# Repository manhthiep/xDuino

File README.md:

xDuino
======

Collection of Arduino-compatible boards

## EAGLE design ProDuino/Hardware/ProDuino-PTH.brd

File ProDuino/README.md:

ProDuino
======

ProDuino - Arduino-compatible board without USB port.

Original design: [SparkFun's Arduino Pro 328](https://www.sparkfun.com/products/10915)

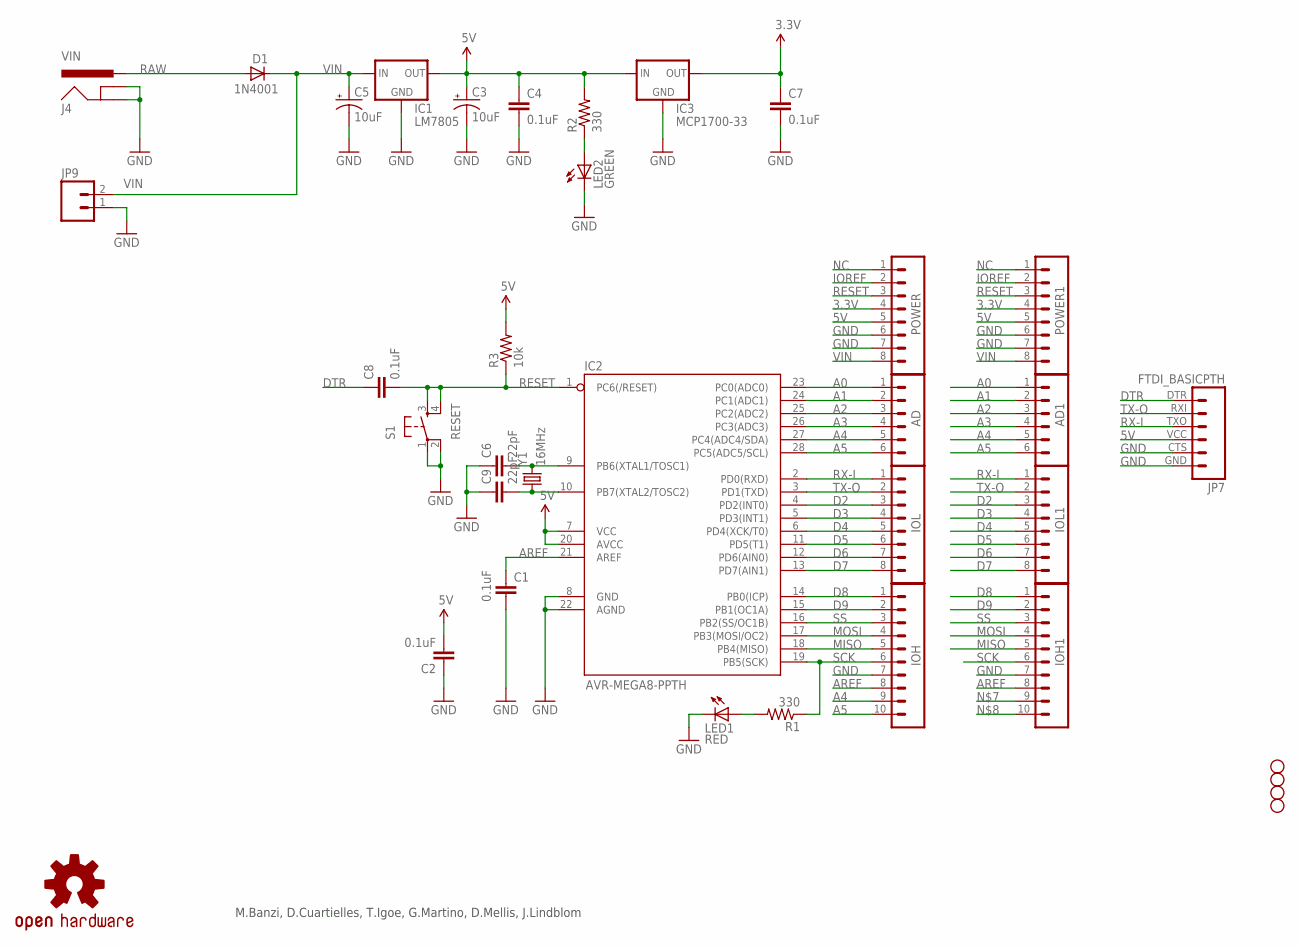
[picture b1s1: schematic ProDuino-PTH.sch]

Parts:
AD, AD1: M06SIP; 1X06
C1, C2, C4, C7, C8: 0.1uF; CAP-PTH-SMALL2
C3, C5: 10uF; CPOL-RADIAL-10UF-25V
C6, C9: 22pF; CAP-PTH-SMALL2
D1: 1N4001; DIODE-1N4001
IC1: LM7805; TO-220-ALT
IC2: AVR-MEGA8-PPTH; DIL28-3
IC3: MCP1700-33; TO-92
IOH, IOH1: M10"; 1X10
IOL, IOL1: M081X08; 1X08
J4: VIN; POWER_JACK_PTH_LOCK
JP3, JP4, JP5, JP6: STAND-OFF
JP7: FTDI_BASICPTH; FTDI_BASIC
JP9: M02POLAR; MOLEX-1X2
LED1: RED; LED5MM
LED2: GREEN; LED5MM
POWER, POWER1: M081X08; 1X08
R1, R2: 330; AXIAL-0.3
R3: 10k; AXIAL-0.3
S1: RESET; TACTILE-PTH
U$7: OSHW-LOGOM; OSHW-LOGO-M
Y1: 16MHz; HC49US

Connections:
3.3V: C7.1, IC3.3 (OUT), POWER.4, POWER1.4
5V: C2.2, C3.1 (+), C4.1, IC1.OUT, IC2.7 (VCC), IC2.20 (AVCC), IC3.2 (IN), JP7.VCC (4), POWER.5, POWER1.5, R2.P$2 (2), R3.P$2 (2)
A0: AD.1, AD1.1, IC2.23 (PC0(ADC0))
A1: AD.2, AD1.2, IC2.24 (PC1(ADC1))
A2: AD.3, AD1.3, IC2.25 (PC2(ADC2))
A3: AD.4, AD1.4, IC2.26 (PC3(ADC3))
A4: AD.5, AD1.5, IC2.27 (PC4(ADC4/SDA)), IOH.9
A5: AD.6, AD1.6, IC2.28 (PC5(ADC5/SCL)), IOH.10
AREF: C1.1, IC2.21 (AREF), IOH.8, IOH1.8
D2: IC2.4 (PD2(INT0)), IOL.3, IOL1.3
D3: IC2.5 (PD3(INT1)), IOL.4, IOL1.4
D4: IC2.6 (PD4(XCK/T0)), IOL.5, IOL1.5
D5: IC2.11 (PD5(T1)), IOL.6, IOL1.6
D6: IC2.12 (PD6(AIN0)), IOL.7, IOL1.7
D7: IC2.13 (PD7(AIN1)), IOL.8, IOL1.8
D8: IC2.14 (PB0(ICP)), IOH.1, IOH1.1
D9: IC2.15 (PB1(OC1A)), IOH.2, IOH1.2
DTR: C8.1, JP7.DTR (1)
GND: C1.2, C2.1, C3.2 (-), C4.2, C5.2 (-), C6.1, C7.2, C9.1, IC1.GND, IC2.8 (GND), IC2.22 (AGND), IC3.1 (GND), IOH.7, IOH1.7, J4.GND, J4.GNDBREAK, JP7.CTS (5), JP7.GND (6), JP9.1, LED1.K (C), LED2.K (C), POWER.6, POWER.7, POWER1.6, POWER1.7, S1.1, S1.2
IOREF: POWER.2, POWER1.2
MISO: IC2.18 (PB4(MISO)), IOH.5, IOH1.5
MOSI: IC2.17 (PB3(MOSI/OC2)), IOH.4, IOH1.4
unnamed: LED1.A, R1.P$2 (2)
unnamed: LED2.A, R2.P$1 (1)
unnamed: C6.2, IC2.9 (PB6(XTAL1/TOSC1)), Y1.2
unnamed: C9.2, IC2.10 (PB7(XTAL2/TOSC2)), Y1.1
NC: POWER.1, POWER1.1
RAW: D1.A, J4.PWR
RESET: C8.2, IC2.1 (PC6(/RESET)), POWER.3, POWER1.3, R3.P$1 (1), S1.3, S1.4
RX-I: IC2.2 (PD0(RXD)), IOL.1, IOL1.1, JP7.TXO (3)
SCK: IC2.19 (PB5(SCK)), IOH.6, IOH1.6, R1.P$1 (1)
SS: IC2.16 (PB2(SS/OC1B)), IOH.3, IOH1.3
TX-O: IC2.3 (PD1(TXD)), IOL.2, IOL1.2, JP7.RXI (2)
VIN: C5.1 (+), D1.C, IC1.IN, JP9.2, POWER.8, POWER1.8

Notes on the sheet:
M.Banzi, D.Cuartielles, T.Igoe, G.Martino, D.Mellis, J.Lindblom

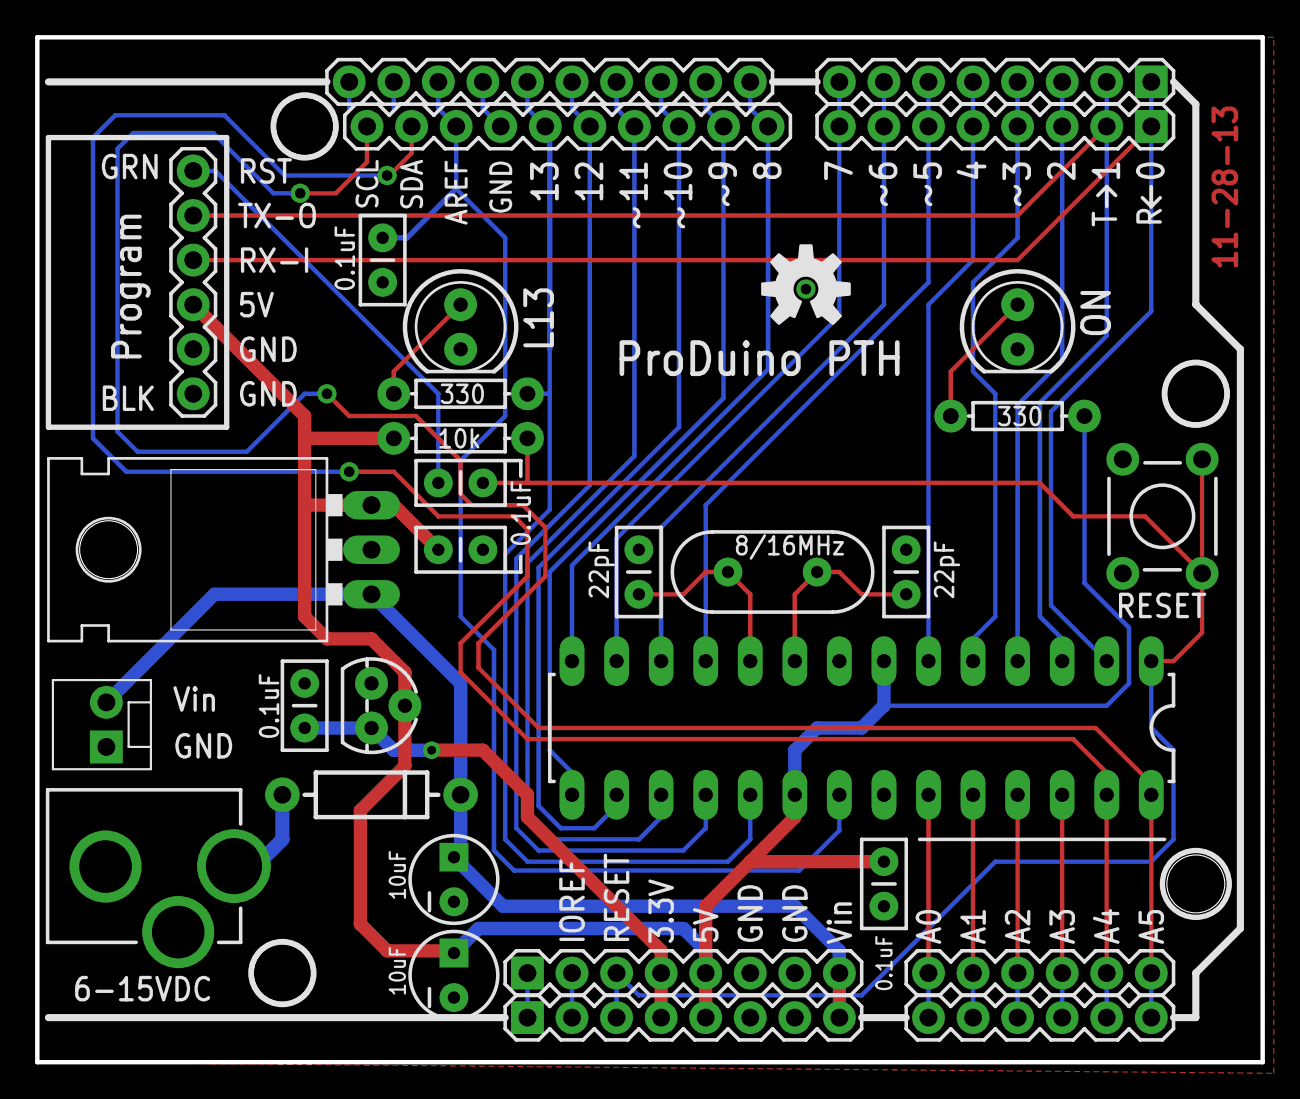
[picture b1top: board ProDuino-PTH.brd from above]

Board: 2 copper layers, 69.8 x 58.4 mm, 36 parts (0 on the bottom side), 34 nets.

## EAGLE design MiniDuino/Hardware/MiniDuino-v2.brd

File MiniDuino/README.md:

MiniDuino
======

MiniDuino - Arduino-compatible board with minimal design.
This board includes FTDI Basic for programming over USB.

It's a stripped down version of SparkFun's ProtoSnap.

Original design: 
[SparkFun's Arduino Pro Mini 328](https://www.sparkfun.com/products/11113)
[SparkFun's ProtoSnap - Pro Mini] (https://www.sparkfun.com/products/10889)

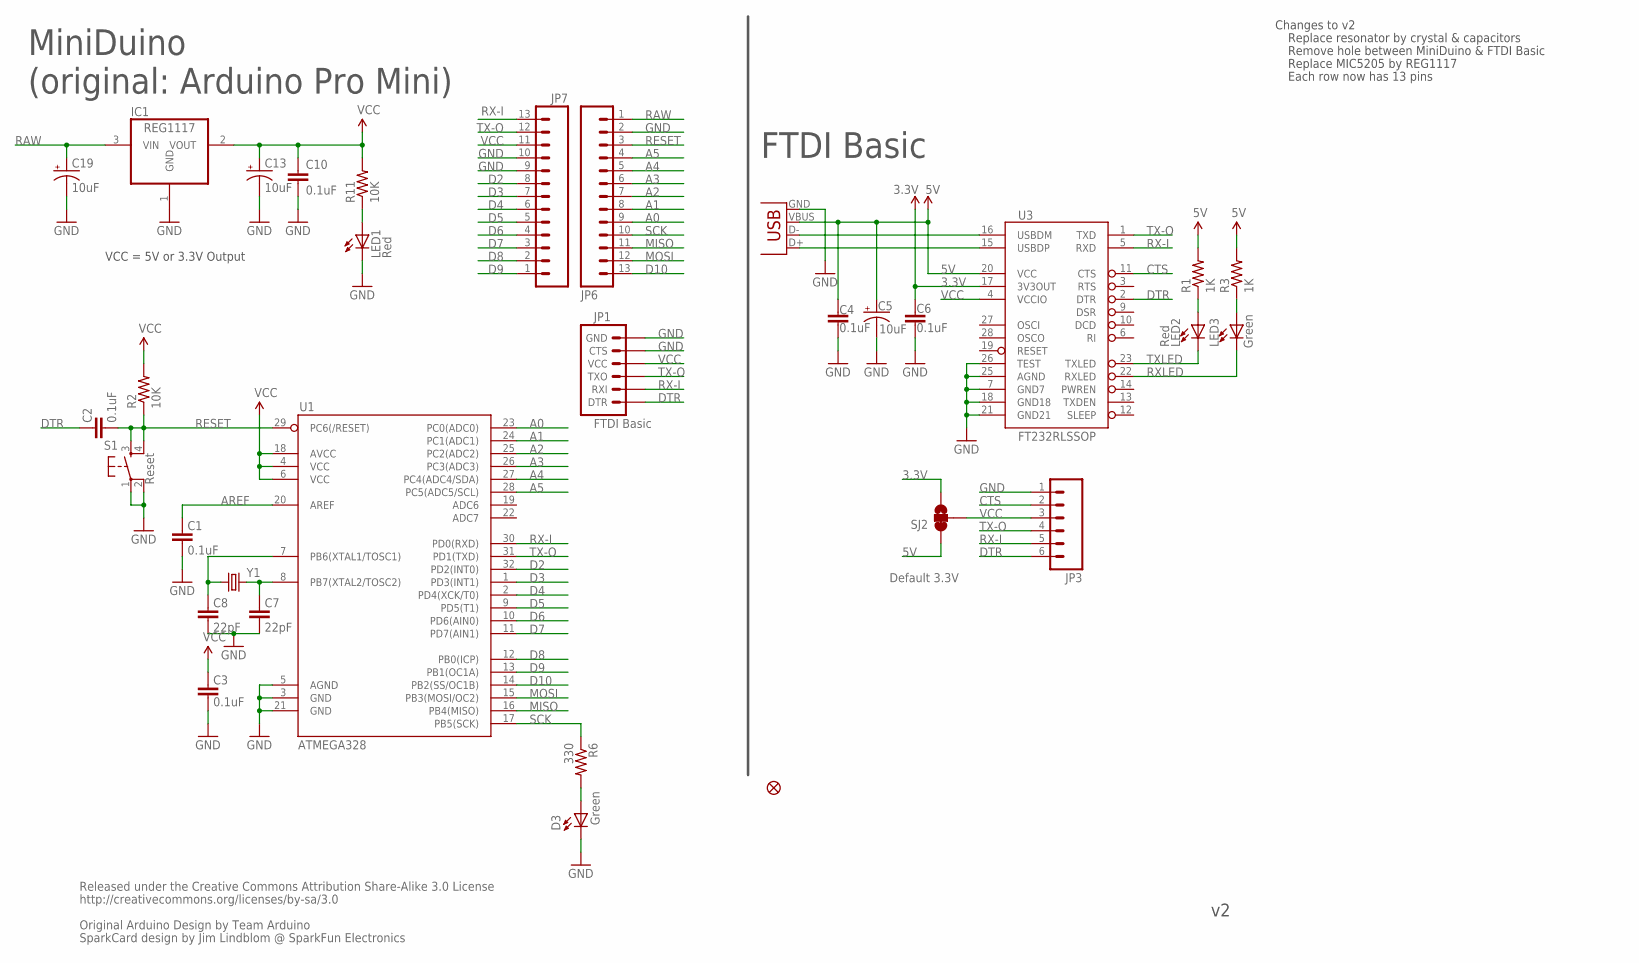
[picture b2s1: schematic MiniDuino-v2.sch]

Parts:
C1, C2, C3, C4, C6, C10: 0.1uF; 0402-CAP
C5, C13, C19: 10uF; EIA3216
C7, C8: 22pF; 0402-CAP
D3: Green; LED-0603
IC1: REG1117; SOT223
JP1: FTDI Basic; 1X06
JP3: M06SIP; 1X06
JP6, JP7: M13; 1X13
JP16: FIDUCIAL1X2.5; FIDUCIAL-1X2.5
LED1, LED2: Red; LED-0603
LED3: Green; LED-0603
R1, R3: 1K; 0603-RES
R2, R11: 10K; 0402-RES
R6: 330; 0402-RES
S1: Reset; TACTILE_SWITCH_SMD
SJ2: SOLDERJUMPER_2WAYS; SJ_3
U1: ATMEGA328; TQFP32-08
U3: FT232RLSSOP; SSOP28DB
X2: USB-SMD-NS; USB-MINIB-NOSTOP
Y1: CRYSTAL5X3; CRYSTAL-SMD-5X3

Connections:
3.3V: C6.1, SJ2.3, U3.17 (3V3OUT)
5V: C4.1, C5.A (+), R1.2, R3.2, SJ2.1, U3.20 (VCC), X2.VBUS
A0: JP6.9, U1.23 (PC0(ADC0))
A1: JP6.8, U1.24 (PC1(ADC1))
A2: JP6.7, U1.25 (PC2(ADC2))
A3: JP6.6, U1.26 (PC3(ADC3))
A4: JP6.5, U1.27 (PC4(ADC4/SDA))
A5: JP6.4, U1.28 (PC5(ADC5/SCL))
AREF: C1.2, U1.20 (AREF)
CTS: JP3.2, U3.11 (CTS)
D2: JP7.8, U1.32 (PD2(INT0))
D3: JP7.7, U1.1 (PD3(INT1))
D4: JP7.6, U1.2 (PD4(XCK/T0))
D5: JP7.5, U1.9 (PD5(T1))
D6: JP7.4, U1.10 (PD6(AIN0))
D7: JP7.3, U1.11 (PD7(AIN1))
D8: JP7.2, U1.12 (PB0(ICP))
D9: JP7.1, U1.13 (PB1(OC1A))
D10: JP6.13, U1.14 (PB2(SS/OC1B))
DTR: C2.2, JP1.1 (DTR), JP3.6, U3.2 (DTR)
GND: C1.1, C3.1, C4.2, C5.C (-), C6.2, C7.1, C8.1, C10.2, C13.C (-), C19.C (-), D3.C, IC1.1 (GND), JP1.5 (CTS), JP1.6 (GND), JP3.1, JP6.2, JP7.9, JP7.10, LED1.C, S1.1, S1.2, U1.3 (GND), U1.5 (AGND), U1.21 (GND), U3.7 (GND7), U3.18 (GND18), U3.21 (GND21), U3.25 (AGND), U3.26 (TEST), X2.GND
MISO: JP6.11, U1.16 (PB4(MISO))
MOSI: JP6.12, U1.15 (PB3(MOSI/OC2))
unnamed: C7.2, U1.8 (PB7(XTAL2/TOSC2)), Y1.3 (2)
unnamed: C8.2, U1.7 (PB6(XTAL1/TOSC1)), Y1.1
unnamed: LED2.A, R1.1
unnamed: LED3.A, R3.1
unnamed: D3.A, R6.2
unnamed: LED1.A, R11.1
RAW: C19.A (+), IC1.3 (VIN), JP6.1
RESET: C2.1, JP6.3, R2.1, S1.3, S1.4, U1.29 (PC6(/RESET))
RX-I: JP1.2 (RXI), JP3.5, JP7.13, U1.30 (PD0(RXD)), U3.5 (RXD)
RXLED: LED3.C, U3.22 (RXLED)
SCK: JP6.10, R6.1, U1.17 (PB5(SCK))
TX-O: JP1.3 (TXO), JP3.4, JP7.12, U1.31 (PD1(TXD)), U3.1 (TXD)
TXLED: LED2.C, U3.23 (TXLED)
USB_D+: U3.15 (USBDP), X2.D+
USB_D-: U3.16 (USBDM), X2.D-
VCC: C3.2, C10.1, C13.A (+), IC1.2 (VOUT), JP1.4 (VCC), JP3.3, JP7.11, R2.2, R11.2, SJ2.2, U1.4 (VCC), U1.6 (VCC), U1.18 (AVCC), U3.4 (VCCIO)

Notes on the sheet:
VCC = 5V or 3.3V Output
Released under the Creative Commons Attribution Share-Alike 3.0 License
http://creativecommons.org/licenses/by-sa/3.0
Original Arduino Design by Team Arduino
SparkCard design by Jim Lindblom @ SparkFun Electronics
MiniDuino (original: Arduino Pro Mini)
Default 3.3V
FTDI Basic
Changes to v2
Replace resonator by crystal & capacitors
Remove hole between MiniDuino & FTDI Basic
Replace MIC5205 by REG1117
Each row now has 13 pins

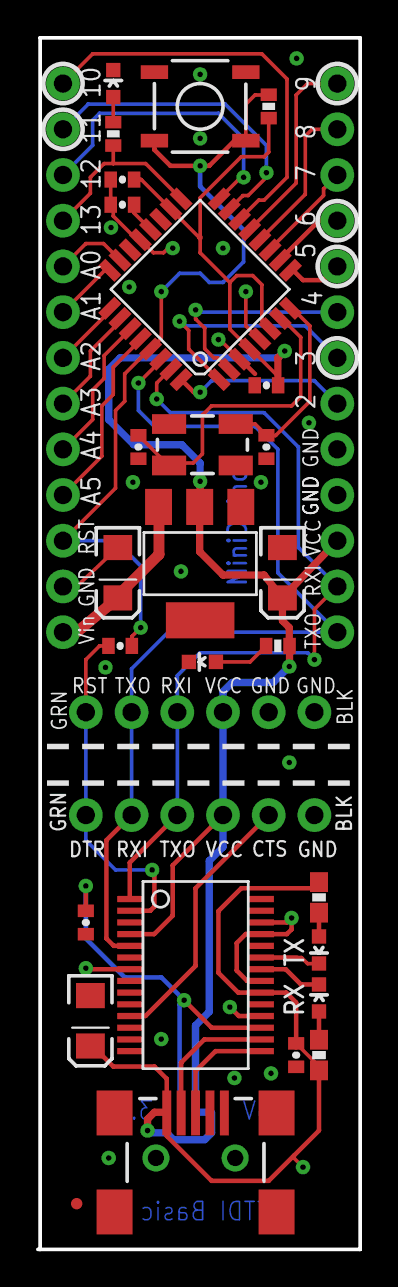
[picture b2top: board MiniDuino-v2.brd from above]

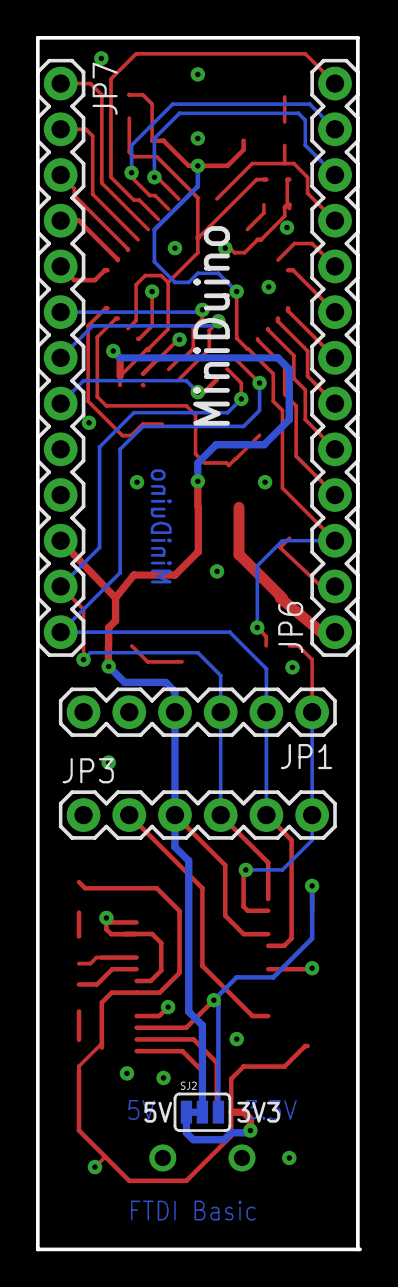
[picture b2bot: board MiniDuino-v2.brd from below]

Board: 2 copper layers, 17.9 x 67.3 mm, 32 parts (5 on the bottom side), 39 nets.

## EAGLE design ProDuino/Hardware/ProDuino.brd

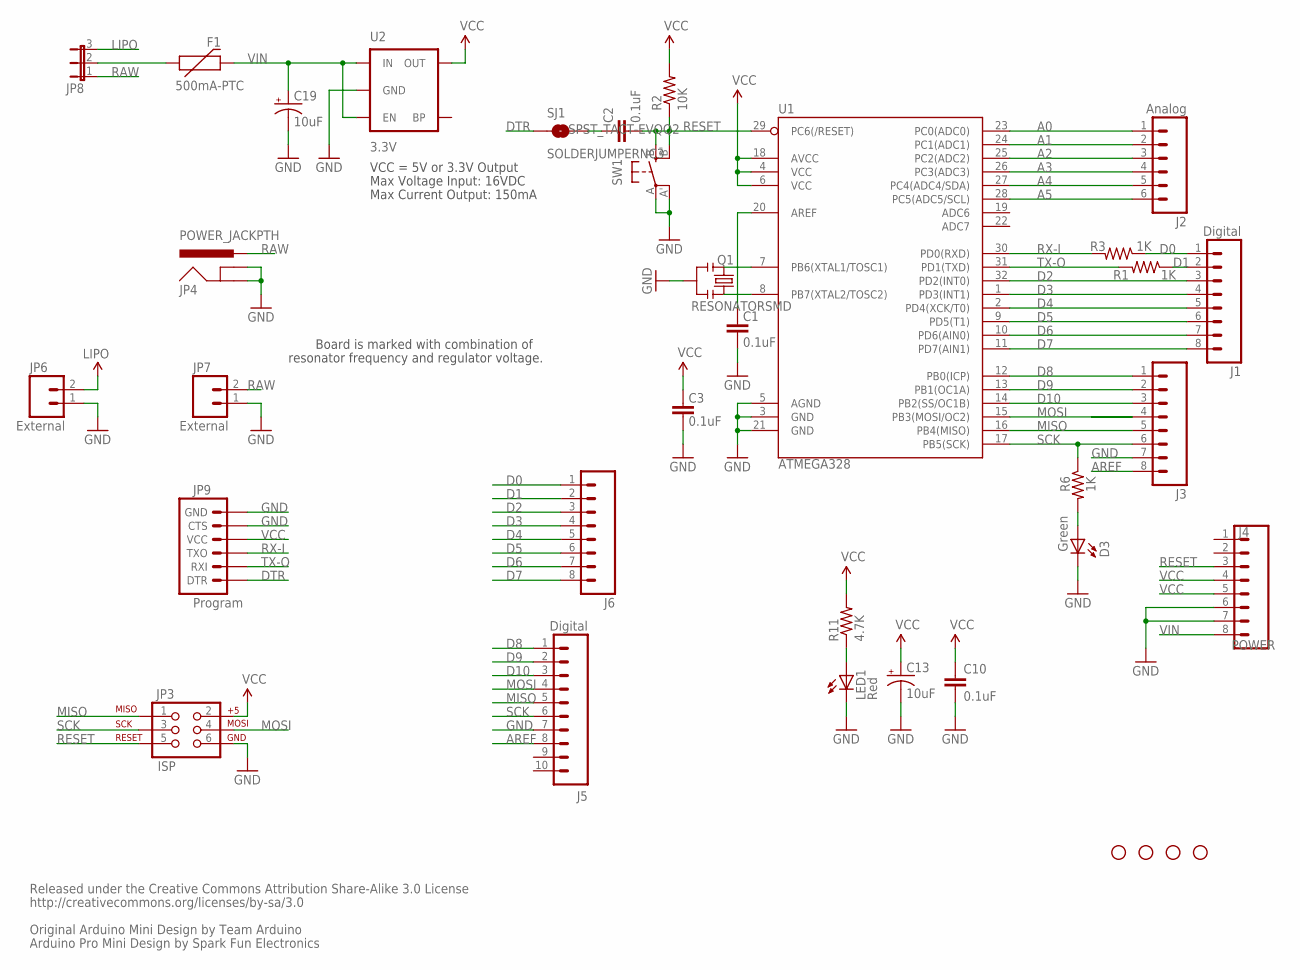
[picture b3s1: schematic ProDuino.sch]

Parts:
C1, C2, C3, C10: 0.1uF; 0603-CAP
C13, C19: 10uF; EIA3216
D3: Green; LED-0603
F1: 500mA-PTC; PTC-1206
J1: Digital; 1X08
J2: Analog; 1X06
J3, J6: M081X08; 1X08
J4: POWER; 1X08
J5: Digital; 1X10
JP3: ISP; 2X3
JP4: POWER_JACKPTH; POWER_JACK_PTH
JP6, JP7: External; 1X02
JP8: JP2E; JP2
JP9: Program; 1X06
LED1: Red; LED-0603
Q1: RESONATORSMD; RESONATOR-SMD
R1, R3, R6: 1K; 0603-RES
R2: 10K; 0603-RES
R11: 4.7K; 0603-RES
SJ1: SOLDERJUMPERNC3; SJ_2S-NOTRACE
SW1: SPST_TACT-EVQQ2; EVQ-Q2
U1: ATMEGA328; TQFP32-08
U2: 3.3V; SOT23-5
U$1, U$3, U$9, U$10: STAND-OFF

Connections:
A0: J2.1, U1.23 (PC0(ADC0))
A1: J2.2, U1.24 (PC1(ADC1))
A2: J2.3, U1.25 (PC2(ADC2))
A3: J2.4, U1.26 (PC3(ADC3))
A4: J2.5, U1.27 (PC4(ADC4/SDA))
A5: J2.6, U1.28 (PC5(ADC5/SCL))
AREF: C1.2, J3.8, J5.8, U1.20 (AREF)
D0: J1.1, J6.1, R3.1
D1: J1.2, J6.2, R1.1
D2: J1.3, J6.3, U1.32 (PD2(INT0))
D3: J1.4, J6.4, U1.1 (PD3(INT1))
D4: J1.5, J6.5, U1.2 (PD4(XCK/T0))
D5: J1.6, J6.6, U1.9 (PD5(T1))
D6: J1.7, J6.7, U1.10 (PD6(AIN0))
D7: J1.8, J6.8, U1.11 (PD7(AIN1))
D8: J3.1, J5.1, U1.12 (PB0(ICP))
D9: J3.2, J5.2, U1.13 (PB1(OC1A))
D10: J3.3, J5.3, U1.14 (PB2(SS/OC1B))
DTR: JP9.1 (DTR), SJ1.1
GND: C1.1, C3.1, C10.2, C13.C (-), C19.C (-), D3.C, J3.7, J4.6, J4.7, J5.7, JP3.6, JP4.GND, JP4.GNDBREAK, JP6.1, JP7.1, JP9.5 (CTS), JP9.6 (GND), LED1.C, Q1.2, SW1.A, SW1.A' (P1), U1.3 (GND), U1.5 (AGND), U1.21 (GND), U2.2 (GND)
LIPO: JP6.2, JP8.3
MISO: J3.5, J5.5, JP3.1, U1.16 (PB4(MISO))
MOSI: J3.4, J5.4, JP3.4, U1.15 (PB3(MOSI/OC2))
unnamed: C2.1, SJ1.2
unnamed: Q1.1, U1.8 (PB7(XTAL2/TOSC2))
unnamed: Q1.3, U1.7 (PB6(XTAL1/TOSC1))
unnamed: D3.A, R6.2
unnamed: F1.1, JP8.2
unnamed: LED1.A, R11.1
RAW: JP4.PWR, JP7.2, JP8.1
RESET: C2.2, J4.3, JP3.5, R2.1, SW1.B (S), SW1.B' (S1), U1.29 (PC6(/RESET))
RX-I: JP9.3 (TXO), R3.2, U1.30 (PD0(RXD))
SCK: J3.6, J5.6, JP3.3, R6.1, U1.17 (PB5(SCK))
TX-O: JP9.2 (RXI), R1.2, U1.31 (PD1(TXD))
VCC: C3.2, C10.1, C13.A (+), J4.4, J4.5, JP3.2, JP9.4 (VCC), R2.2, R11.2, U1.4 (VCC), U1.6 (VCC), U1.18 (AVCC), U2.5 (OUT)
VIN: C19.A (+), F1.2, J4.8, U2.1 (IN), U2.3 (EN)

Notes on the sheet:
Released under the Creative Commons Attribution Share-Alike 3.0 License
http://creativecommons.org/licenses/by-sa/3.0
Original Arduino Mini Design by Team Arduino
Arduino Pro Mini Design by Spark Fun Electronics
VCC = 5V or 3.3V Output
Max Voltage Input: 16VDC
Max Current Output: 150mA
Board is marked with combination of
resonator frequency and regulator voltage.

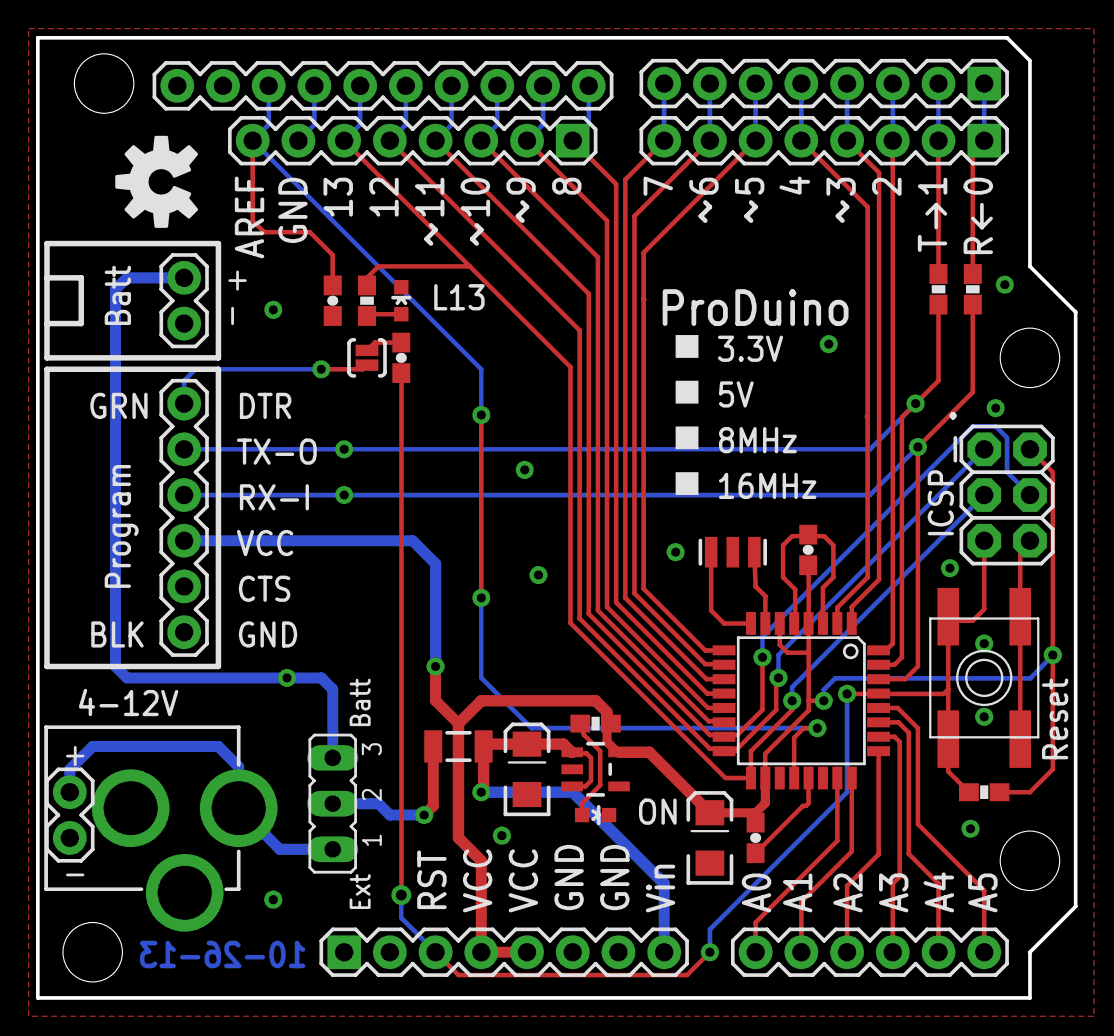
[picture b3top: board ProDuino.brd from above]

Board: 2 copper layers, 57.7 x 53.3 mm, 36 parts (0 on the bottom side), 36 nets.

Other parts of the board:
U$2: OSHW-LOGO-M

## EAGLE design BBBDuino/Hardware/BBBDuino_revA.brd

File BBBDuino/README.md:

BBBDuino
======

BBBDuino - Arduino Cape for BeagleBone Black (BBB)

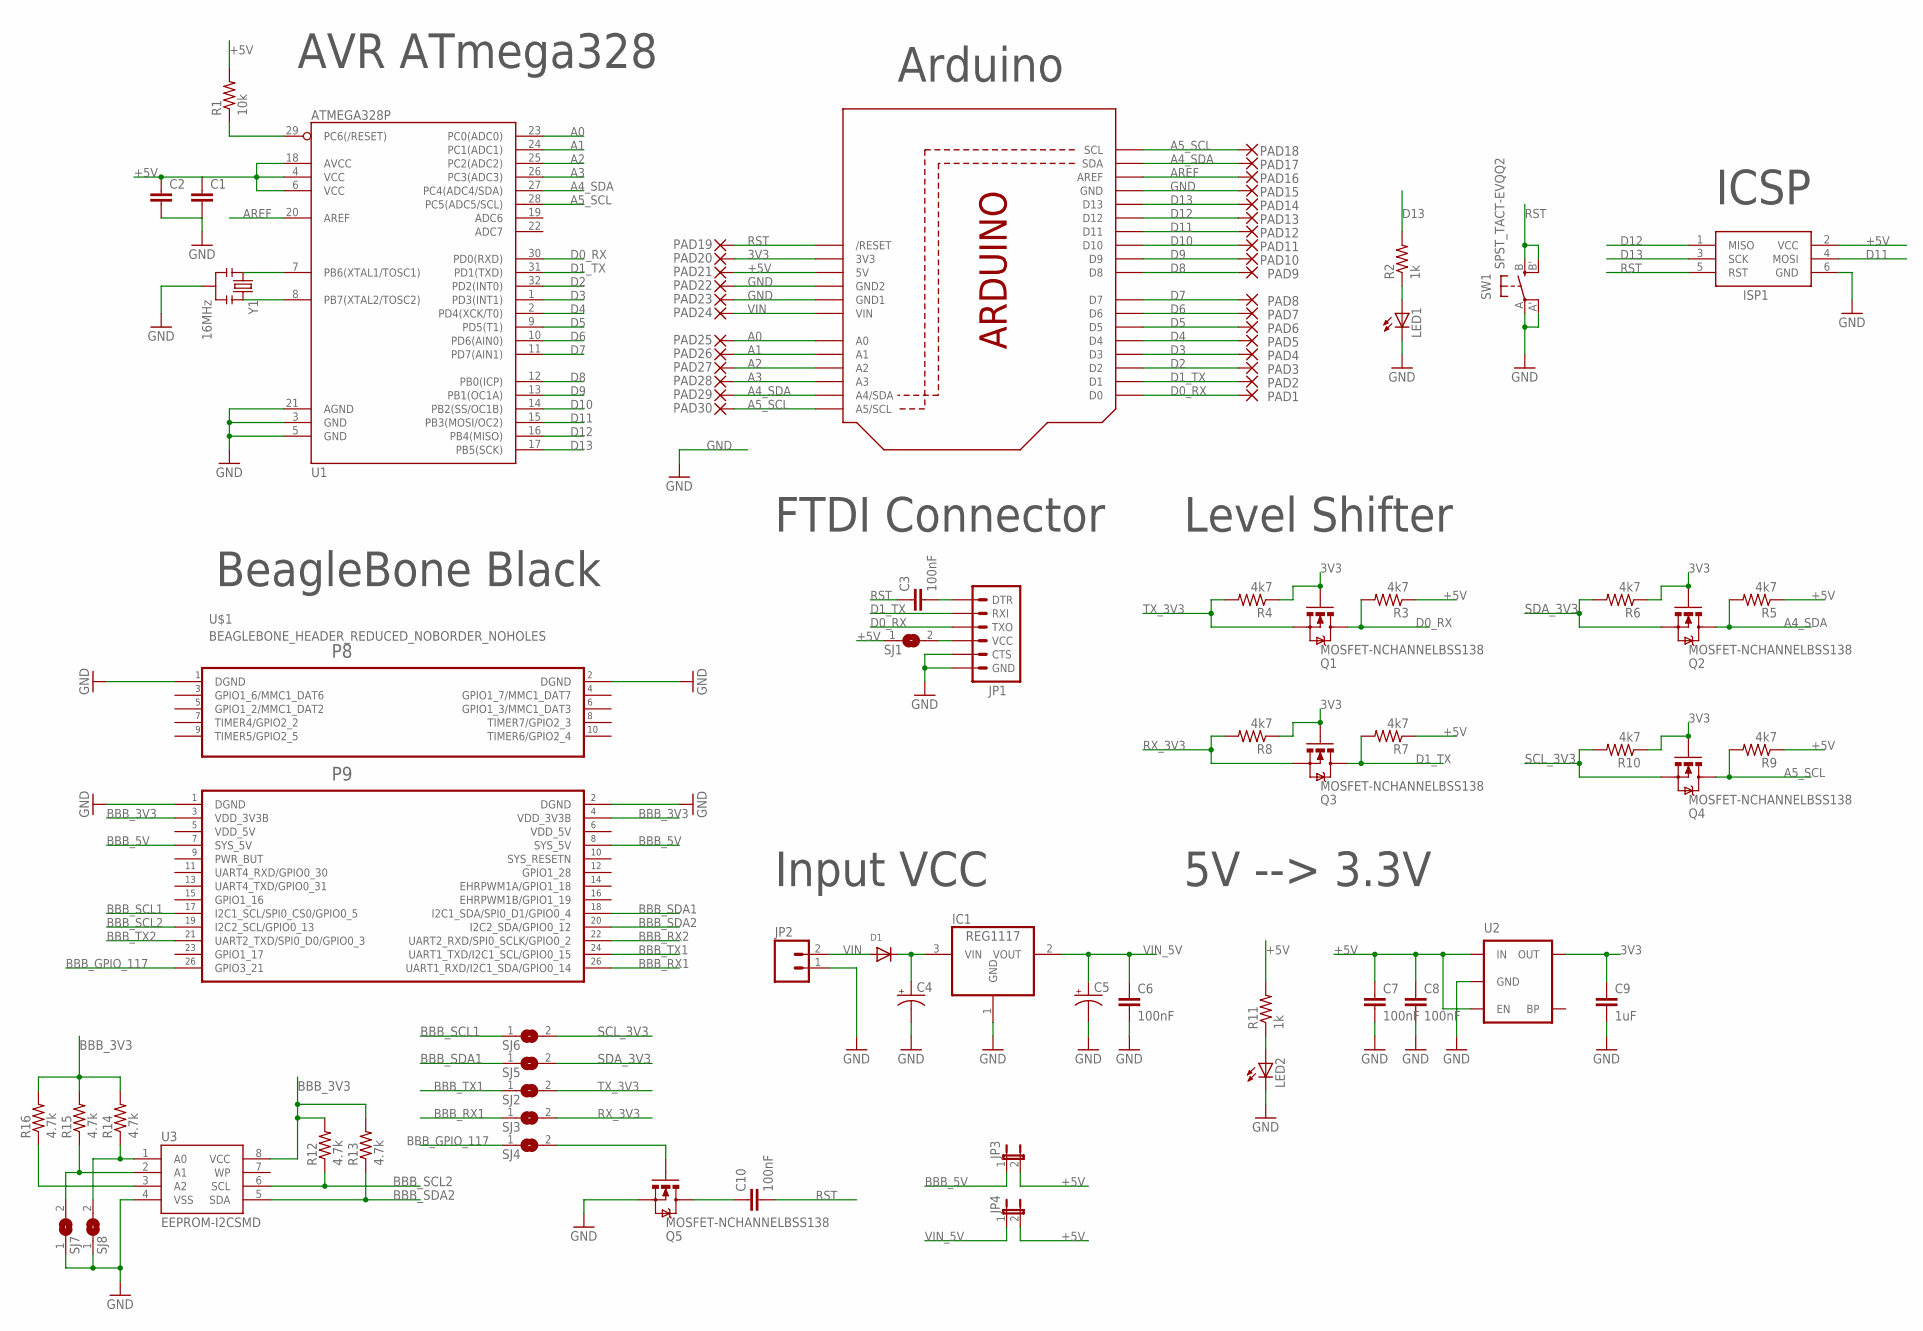
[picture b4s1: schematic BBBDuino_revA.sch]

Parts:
C1, C2: CAP0603-CAP; 0603-CAP
C3, C6, C7, C8, C10: 100nF; 0603-CAP
C4, C5: CAP_POLD; PANASONIC_D
C9: 1uF; 0603-CAP
D1: DIODESMA; SMADIODE
IC1: REG1117; SOT223
ISP1: AVRISP-6; AVRISP
JP1: ARDUINO_SERIAL_PROGRAMPTH; 1X06
JP2: M02PTH; 1X02
JP3, JP4: JUMPER-2PTH; 1X02
LED1, LED2: LEDCHIP-LED0603; CHIP-LED0603
PAD1, PAD2, PAD3, PAD4, PAD5, PAD6, PAD7, PAD8, PAD9, PAD10, PAD11, PAD12, PAD13, PAD14, PAD15, PAD16, PAD17, PAD18, PAD19, PAD20, PAD21, PAD22, PAD23, PAD24, PAD25, PAD26, PAD27, PAD28, PAD29, PAD30: 1,6/0,9
Q1, Q2, Q3, Q4, Q5: MOSFET-NCHANNELBSS138; SOT23
R1: 10k; 0603-RES
R2, R11: 1k; 0603-RES
R3, R4, R5, R6, R7, R8, R9, R10: 4k7; 0603-RES
R12, R13, R14, R15, R16: 4.7k; 0603-RES
SJ1, SJ2, SJ3, SJ4, SJ5, SJ6, SJ7, SJ8: SJ
SW1: SPST_TACT-EVQQ2; EVQ-Q2
U1: ATMEGA328P; TQFP32-08
U2: MIC52053.3V; SOT23-5
U3: EEPROM-I2CSMD; SO08
U$1: BEAGLEBONE_HEADER_REDUCED_NOBORDER_NOHOLES
U$2: ARDUINO_NOIOREF_NOBORDER_HOLES_NAMES; ARDUINO_NOIOREF_BORDER_HOLES_NAMES
Y1: 16MHz; RESONATOR-SMD

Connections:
3V3: C9.1, PAD20.1, Q1.1 (G), Q2.1 (G), Q3.1 (G), Q4.1 (G), R4.1, R6.1, R8.1, R10.1, U2.5 (OUT), U$2.3V (3V3)
+5V: C1.1, C2.1, C7.1, C8.1, ISP1.2 (VCC), JP3.2, JP4.2, PAD21.1, R1.2, R3.1, R5.1, R7.1, R9.1, R11.2, SJ1.1, U1.4 (VCC), U1.6 (VCC), U1.18 (AVCC), U2.1 (IN), U2.3 (EN), U$2.5V
A0: PAD25.1, U1.23 (PC0(ADC0)), U$2.A0
A1: PAD26.1, U1.24 (PC1(ADC1)), U$2.A1
A2: PAD27.1, U1.25 (PC2(ADC2)), U$2.A2
A3: PAD28.1, U1.26 (PC3(ADC3)), U$2.A3
A4_SDA: PAD17.1, PAD29.1, Q2.3 (D), R5.2, U1.27 (PC4(ADC4/SDA)), U$2.A4 (A4/SDA), U$2.SDA
A5_SCL: PAD18.1, PAD30.1, Q4.3 (D), R9.2, U1.28 (PC5(ADC5/SCL)), U$2.A5 (A5/SCL), U$2.SCL
AREF: PAD16.1, U1.20 (AREF), U$2.AREF
BBB_3V3: R12.2, R13.2, R14.2, R15.2, R16.2, U3.8 (VCC), U$1.P9_3 (VDD_3V3B), U$1.P9_4 (VDD_3V3B)
BBB_5V: JP3.1, U$1.P9_7 (SYS_5V), U$1.P9_8 (SYS_5V)
BBB_GPIO_117: SJ4.1, U$1.P9_25 (GPIO3_21)
BBB_RX1: SJ3.1, U$1.P9_26 (UART1_RXD/I2C1_SDA/GPIO0_14)
BBB_RX2: U$1.P9_22 (UART2_RXD/SPI0_SCLK/GPIO0_2)
BBB_SCL1: SJ6.1, U$1.P9_17 (I2C1_SCL/SPI0_CS0/GPIO0_5)
BBB_SCL2: R12.1, U3.6 (SCL), U$1.P9_19 (I2C2_SCL/GPIO0_13)
BBB_SDA1: SJ5.1, U$1.P9_18 (I2C1_SDA/SPI0_D1/GPIO0_4)
BBB_SDA2: R13.1, U3.5 (SDA), U$1.P9_20 (I2C2_SDA/GPIO0_12)
BBB_TX1: SJ2.1, U$1.P9_24 (UART1_TXD/I2C1_SCL/GPIO0_15)
BBB_TX2: U$1.P9_21 (UART2_TXD/SPI0_D0/GPIO0_3)
D0_RX: JP1.3 (TXO), PAD1.1, Q1.3 (D), R3.2, U1.30 (PD0(RXD)), U$2.D0
D1_TX: JP1.2 (RXI), PAD2.1, Q3.3 (D), R7.2, U1.31 (PD1(TXD)), U$2.D1
D2: PAD3.1, U1.32 (PD2(INT0)), U$2.D2
D3: PAD4.1, U1.1 (PD3(INT1)), U$2.D3
D4: PAD5.1, U1.2 (PD4(XCK/T0)), U$2.D4
D5: PAD6.1, U1.9 (PD5(T1)), U$2.D5
D6: PAD7.1, U1.10 (PD6(AIN0)), U$2.D6
D7: PAD8.1, U1.11 (PD7(AIN1)), U$2.D7
D8: PAD9.1, U1.12 (PB0(ICP)), U$2.D8
D9: PAD10.1, U1.13 (PB1(OC1A)), U$2.D9
D10: PAD11.1, U1.14 (PB2(SS/OC1B)), U$2.D10
D11: ISP1.4 (MOSI), PAD12.1, U1.15 (PB3(MOSI/OC2)), U$2.D11
D12: ISP1.1 (MISO), PAD13.1, U1.16 (PB4(MISO)), U$2.D12
D13: ISP1.3 (SCK), PAD14.1, R2.2, U1.17 (PB5(SCK)), U$2.D13
GND: C1.2, C2.2, C4.-, C5.-, C6.2, C7.2, C8.2, C9.2, IC1.1 (GND), ISP1.6 (GND), JP1.5 (CTS), JP1.6 (GND), JP2.1, LED1.C, LED2.C, PAD15.1, PAD22.1, PAD23.1, Q5.2 (S), SJ7.1, SJ8.1, SW1.A, SW1.A' (P1), U1.3 (GND), U1.5 (GND), U1.21 (AGND), U2.2 (GND), U3.4 (VSS), U$1.P8_1 (DGND), U$1.P8_2 (DGND), U$1.P9_1 (DGND), U$1.P9_2 (DGND), U$2.GND, U$2.GND1, U$2.GND2, Y1.2
unnamed: U1.7 (PB6(XTAL1/TOSC1)), Y1.1
unnamed: R1.1, U1.29 (PC6(/RESET))
unnamed: C3.2, JP1.1 (DTR)
unnamed: U1.8 (PB7(XTAL2/TOSC2)), Y1.3
unnamed: LED1.A, R2.1
unnamed: LED2.A, R11.1
unnamed: C4.+, D1.C, IC1.3 (VIN)
unnamed: JP1.4 (VCC), SJ1.2
unnamed: C10.1, Q5.3 (D)
unnamed: Q5.1 (G), SJ4.2
unnamed: R14.1, SJ8.2, U3.1 (A0)
unnamed: R15.1, SJ7.2, U3.2 (A1)
unnamed: R16.1, U3.3 (A2)
RST: C3.1, C10.2, ISP1.5 (RST), PAD19.1, SW1.B (S), SW1.B' (S1), U$2.RESET (/RESET)
RX_3V3: Q3.2 (S), R8.2, SJ3.2
SCL_3V3: Q4.2 (S), R10.2, SJ6.2
SDA_3V3: Q2.2 (S), R6.2, SJ5.2
TX_3V3: Q1.2 (S), R4.2, SJ2.2
VDD_5V: U$1.P9_5 (VDD_5V), U$1.P9_6 (VDD_5V)
VIN: D1.A, JP2.2, PAD24.1, U$2.VIN
VIN_5V: C5.+, C6.1, IC1.2 (VOUT), JP4.1

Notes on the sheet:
BeagleBone Black
Arduino
AVR ATmega328
FTDI Connector
Level Shifter
Input VCC
5V --> 3.3V
ICSP

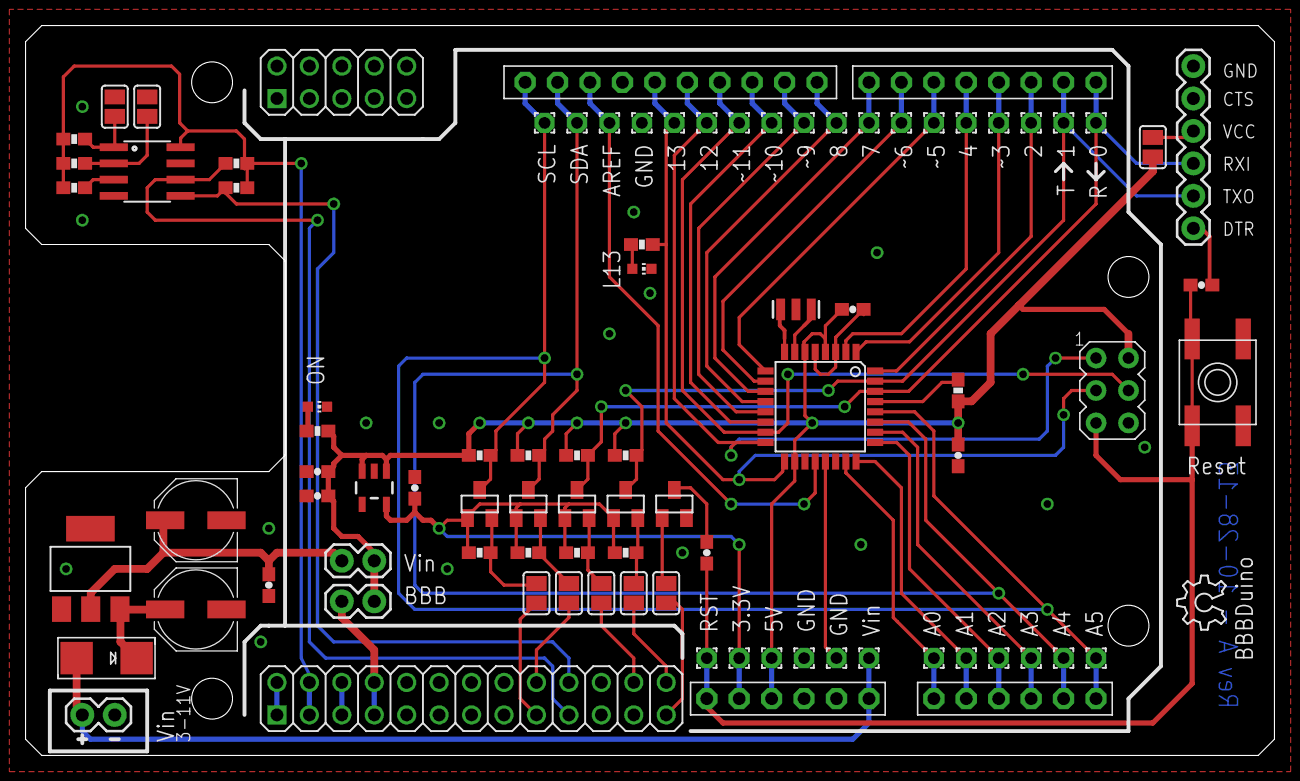
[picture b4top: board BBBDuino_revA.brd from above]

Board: 2 copper layers, 97.8 x 57.1 mm, 86 parts (0 on the bottom side), 54 nets.

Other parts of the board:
LOGO1: OSHW_LOGO_6MILX0150-NT; OSHW_6X150_NOTEXT

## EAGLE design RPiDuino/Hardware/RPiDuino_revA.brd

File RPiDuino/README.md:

RPiDuino
======

RPiDuino - Raspberry Pi extension board which is compatible with Arduino

Original design: [RPi-ShieldBridge](http://www.github.com/watterott/RPi-ShieldBridge)

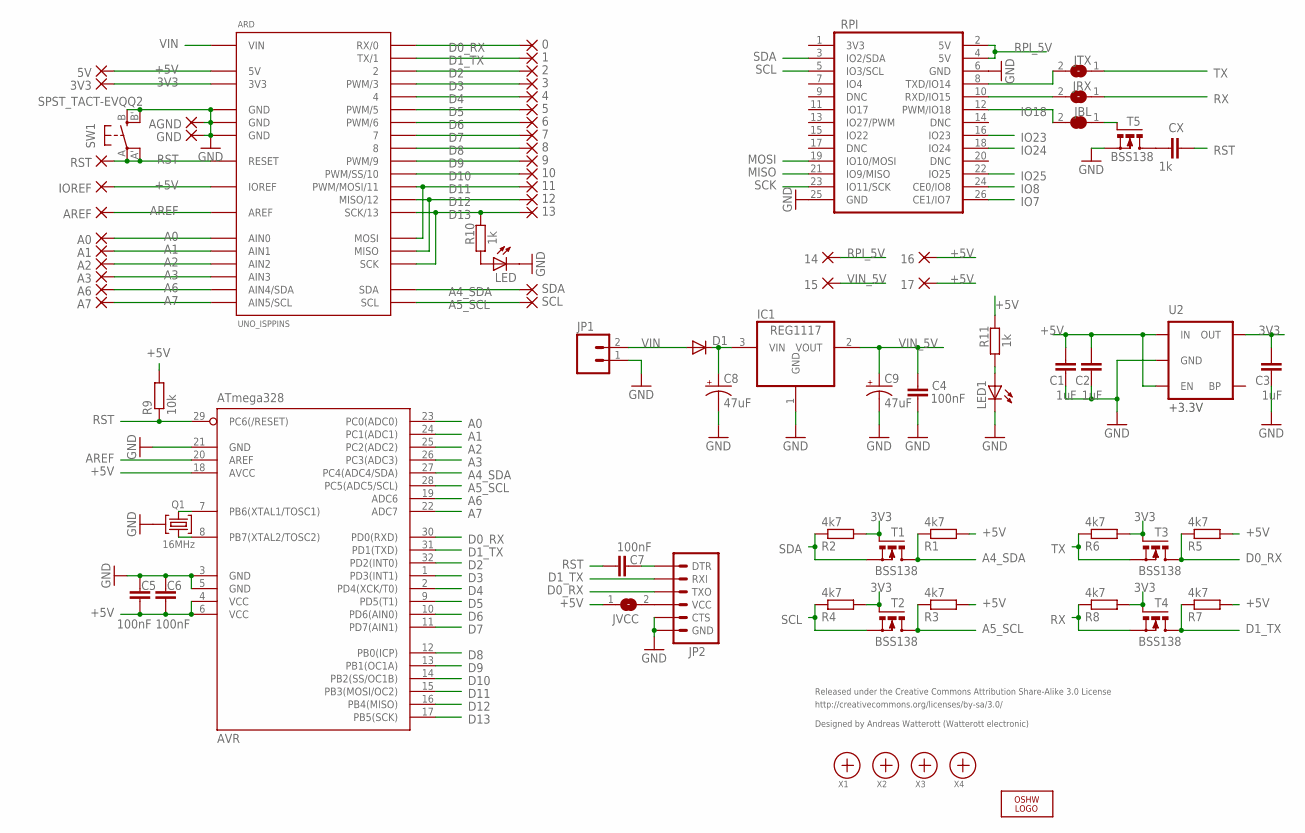
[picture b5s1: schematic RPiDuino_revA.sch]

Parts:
0, 1, 2, 3, 3V3, 4, 5, 5V, 6, 7, 8, 9, 10, 11, 12, 13, 14, 15, 16, 17: WIREPAD1,6/0,9; 1,6/0,9
A0, A1, A2, A3, A6, A7: WIREPAD1,6/0,9; 1,6/0,9
AGND: WIREPAD1,6/0,9; 1,6/0,9
ARD: UNO_ISPPINS; UNO_ISP3
AREF: WIREPAD1,6/0,9; 1,6/0,9
AVR: ATmega328; TQFP32-08
C1, C2, C3: 1uF; C0603
C4, C5, C6, C7: 100nF; C0603
C8, C9: 47uF; PANASONIC_D
CX: 1k; C0603
D1: DIODESMA; SMA-DIODE
GND: WIREPAD1,6/0,9; 1,6/0,9
IC1: REG1117; SOT223
IOREF: WIREPAD1,6/0,9; 1,6/0,9
JBL: SJ
JP1: M02PTH; 1X02
JP2: ARDUINO_SERIAL_PROGRAMPTH; 1X06
JRX: SJ
JTX: SJ
JVCC: SJ
LED, LED1: LEDCHIPLED_0603; CHIPLED_0603
LOGO1: OSHW_LOGO_6MILX0150-NT; OSHW_6X150_NOTEXT
Q1: 16MHz; SMD_OSC_35X15
R1, R2, R3, R4, R5, R6, R7, R8: 4k7; R0603
R9: 10k; R0603
R10, R11: 1k; R0603
RPI: RPI
RST: WIREPAD1,6/0,9; 1,6/0,9
SCL: WIREPAD1,6/0,9; 1,6/0,9
SDA: WIREPAD1,6/0,9; 1,6/0,9
SW1: SPST_TACT-EVQQ2; EVQ-Q2
T1, T2, T3, T4, T5: BSS138; MICRO3
U2: MIC52053.3V; SOT23-5
X1, X2, X3, X4: PASSER

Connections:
3V3: 3V3.1, ARD.3V3, C3.1, R2.2, R4.2, R6.2, R8.2, T1.1 (G), T2.1 (G), T3.1 (G), T4.1 (G), U2.5 (OUT)
+5V: 5V.1, 16.1, 17.1, ARD.5V, ARD.IOREF, AVR.4 (VCC), AVR.6 (VCC), AVR.18 (AVCC), C1.1, C2.1, C5.1, C6.1, IOREF.1, JVCC.1, R1.2, R3.2, R5.2, R7.2, R9.2, R11.1, U2.1 (IN), U2.3 (EN)
A0: A0.1, ARD.AIN0, AVR.23 (PC0(ADC0))
A1: A1.1, ARD.AIN1, AVR.24 (PC1(ADC1))
A2: A2.1, ARD.AIN2, AVR.25 (PC2(ADC2))
A3: A3.1, ARD.AIN3, AVR.26 (PC3(ADC3))
A4_SDA: ARD.SDA, AVR.27 (PC4(ADC4/SDA)), R1.1, SDA.1, T1.3 (D)
A5_SCL: ARD.SCL, AVR.28 (PC5(ADC5/SCL)), R3.1, SCL.1, T2.3 (D)
A6: A6.1, ARD.AIN4 (AIN4/SDA), AVR.19 (ADC6)
A7: A7.1, ARD.AIN5 (AIN5/SCL), AVR.22 (ADC7)
AREF: ARD.AREF, AREF.1, AVR.20 (AREF)
D0_RX: 0.1, ARD.0 (RX/0), AVR.30 (PD0(RXD)), JP2.3 (TXO), R5.1, T3.3 (D)
D1_TX: 1.1, ARD.1 (TX/1), AVR.31 (PD1(TXD)), JP2.2 (RXI), R7.1, T4.3 (D)
D2: 2.1, ARD.2, AVR.32 (PD2(INT0))
D3: 3.1, ARD.3 (PWM/3), AVR.1 (PD3(INT1))
D4: 4.1, ARD.4, AVR.2 (PD4(XCK/T0))
D5: 5.1, ARD.5 (PWM/5), AVR.9 (PD5(T1))
D6: 6.1, ARD.6 (PWM/6), AVR.10 (PD6(AIN0))
D7: 7.1, ARD.7, AVR.11 (PD7(AIN1))
D8: 8.1, ARD.8, AVR.12 (PB0(ICP))
D9: 9.1, ARD.9 (PWM/9), AVR.13 (PB1(OC1A))
D10: 10.1, ARD.10 (PWM/SS/10), AVR.14 (PB2(SS/OC1B))
D11: 11.1, ARD.11 (PWM/MOSI/11), ARD.MOSI, AVR.15 (PB3(MOSI/OC2))
D12: 12.1, ARD.12 (MISO/12), ARD.MISO, AVR.16 (PB4(MISO))
D13: 13.1, ARD.13 (SCK/13), ARD.SCK, AVR.17 (PB5(SCK)), R10.1
DTR: C7.1, JP2.1 (DTR)
GND: AGND.1, ARD.GND@1 (GND), ARD.GND@2 (GND), ARD.GND@3 (GND), AVR.3 (GND), AVR.5 (GND), AVR.21 (GND), C1.2, C2.2, C3.2, C4.2, C5.2, C6.2, C8.-, C9.-, GND.1, IC1.1 (GND), JP1.1, JP2.5 (CTS), JP2.6 (GND), LED.C, LED1.C, Q1.GND, RPI.6 (GND), RPI.25 (GND), SW1.B (S), SW1.B' (S1), T5.2 (S), U2.2 (GND)
IO7: RPI.26 (CE1/IO7)
IO8: RPI.24 (CE0/IO8)
IO18: JBL.2, RPI.12 (PWM/IO18)
IO23: RPI.16 (IO23)
IO24: RPI.18 (IO24)
IO25: RPI.22 (IO25)
MISO: RPI.21 (IO9/MISO)
MOSI: RPI.19 (IO10/MOSI)
unnamed: AVR.8 (PB7(XTAL2/TOSC2)), Q1.2
unnamed: AVR.7 (PB6(XTAL1/TOSC1)), Q1.1
unnamed: LED1.A, R11.2
unnamed: C8.+, D1.C, IC1.3 (VIN)
unnamed: JP2.4 (VCC), JVCC.2
unnamed: CX.1, T5.3 (D)
unnamed: LED.A, R10.2
RPI_5V: 14.1, RPI.2 (5V), RPI.4 (5V)
RPI_RST: JBL.1, T5.1 (G)
RST: ARD.RST (RESET), AVR.29 (PC6(/RESET)), C7.2, CX.2, R9.1, RST.1, SW1.A, SW1.A' (P1)
RX: JRX.1, R8.1, T4.2 (S)
RX_IO15: JRX.2, RPI.10 (RXD/IO15)
SCK: RPI.23 (IO11/SCK)
SCL: R4.1, RPI.5 (IO3/SCL), T2.2 (S)
SDA: R2.1, RPI.3 (IO2/SDA), T1.2 (S)
TX: JTX.1, R6.1, T3.2 (S)
TX_IO14: JTX.2, RPI.8 (TXD/IO14)
VIN: ARD.VIN, D1.A, JP1.2
VIN_5V: 15.1, C4.1, C9.+, IC1.2 (VOUT)

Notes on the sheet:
Released under the Creative Commons Attribution Share-Alike 3.0 License
http://creativecommons.org/licenses/by-sa/3.0/
Designed by Andreas Watterott (Watterott electronic)
+3.3V

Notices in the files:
parts and their libraries:
SparkFun-DigitalIC: Licensing: CC v3.0 Share-Alike You are welcome to use this library for commercial purposes.
